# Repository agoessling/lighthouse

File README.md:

lighthouse
==========

48 Output Diasy-Chainable LED Driver.

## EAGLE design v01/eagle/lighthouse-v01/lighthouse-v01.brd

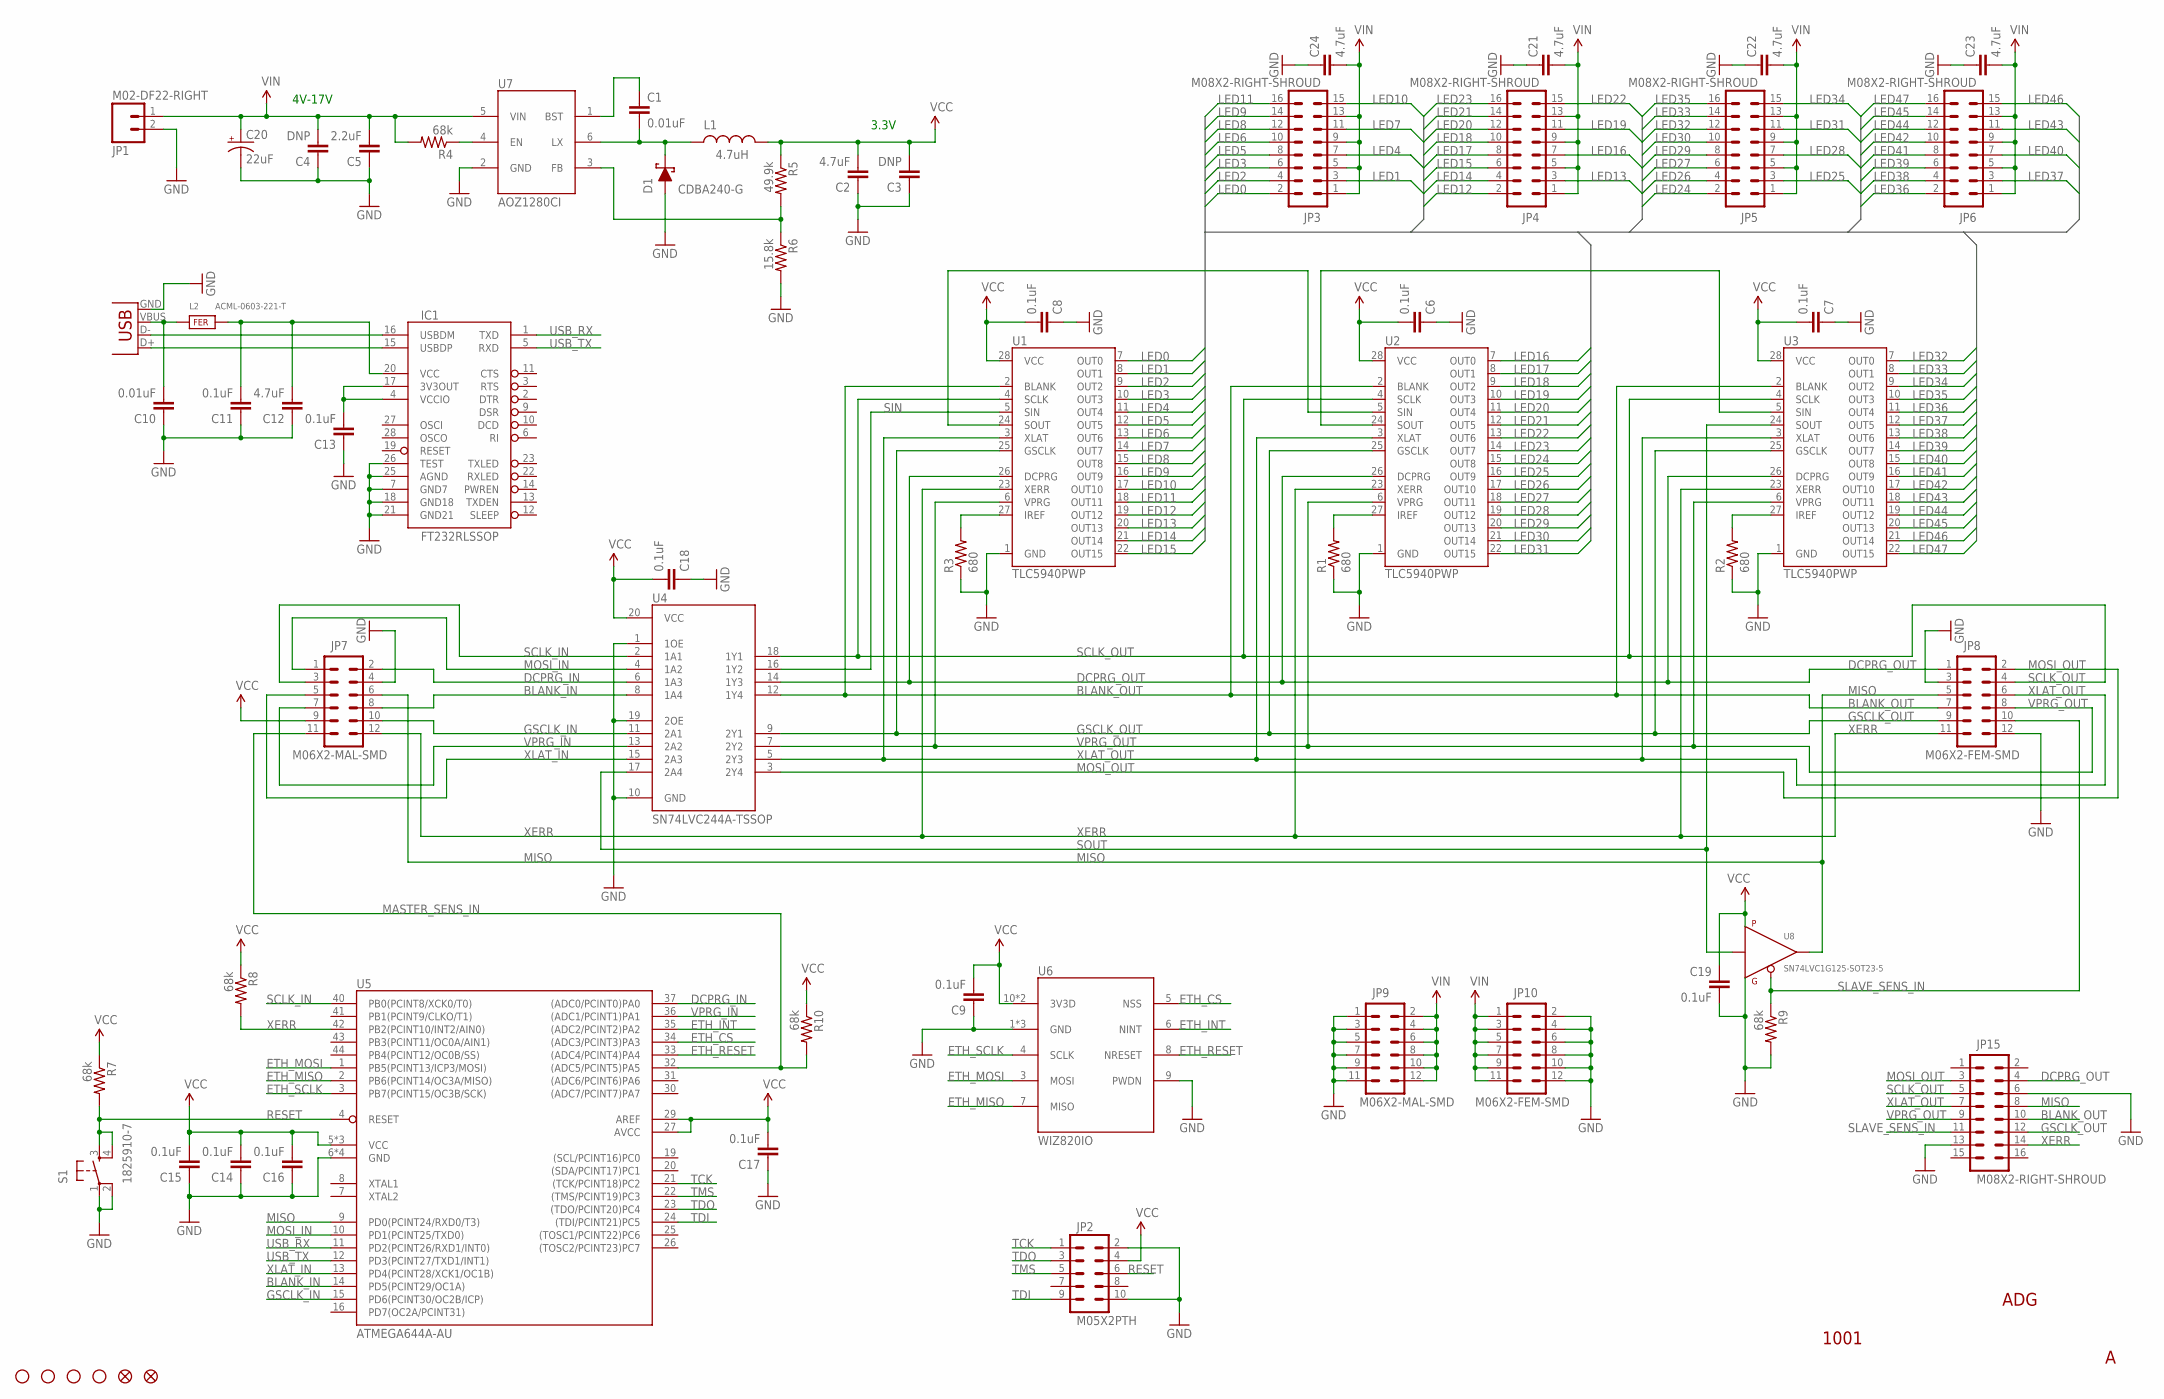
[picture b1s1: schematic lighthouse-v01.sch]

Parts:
C1, C10: 0.01uF; 0603-CAP
C2, C12: 4.7uF; 0805
C3, C4: DNP; 0805
C5: 2.2uF; 0805
C6, C7, C8, C9, C11, C13, C14, C15, C16, C17, C18, C19: 0.1uF; 0603-CAP
C20: 22uF; NIPPON_F80
C21, C22, C23, C24: 4.7uF; 1206
D1: CDBA240-G; DIODE-SMA
IC1: FT232RLSSOP; SSOP28DB
JP1: M02-DF22-RIGHT
JP2: M05X2PTH; AVR_ICSP
JP3, JP4, JP5, JP6, JP15: M08X2-RIGHT-SHROUD; 2X8-RIGHT-SHROUD
JP7, JP9: M06X2-MAL-SMD; 2X6-SMD
JP8, JP10: M06X2-FEM-SMD; 2X6-SMD
JP11, JP12, JP13, JP14: STAND-OFF
JP16, JP17: FIDUCIAL1.5X3; FIDUCIAL-1.5X3
L1: 4.7uH; SRN6045
L2: ACML-0603-221-T; 0603
R1, R2, R3: 680; 0603-RES
R4, R7, R8, R9, R10: 68k; 0603-RES
R5: 49.9k; 0603-RES
R6: 15.8k; 0603-RES
S1: 1825910-7; TACTILE-PTH
U1, U2, U3: TLC5940PWP; TSSOP28-GROUNDPAD
U4: SN74LVC244A-TSSOP; TSSOP-20
U5: ATMEGA644A-AU; TQFP-44
U6: WIZ820IO
U7: AOZ1280CI; SOT23-6
U8: SN74LVC1G125-SOT23-5; SOT23-5
X1: USBSMD; USB-MINIB

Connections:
BLANK_IN: JP7.8, U4.8 (1A4), U5.14 (PD5(PCINT29/OC1A))
BLANK_OUT: JP8.7, JP15.10, U1.2 (BLANK), U2.2 (BLANK), U3.2 (BLANK), U4.12 (1Y4)
DCPRG_IN: JP7.2, U4.6 (1A3), U5.37 ((ADC0/PCINT0)PA0)
DCPRG_OUT: JP8.1, JP15.4, U1.26 (DCPRG), U2.26 (DCPRG), U3.26 (DCPRG), U4.14 (1Y3)
ETH_CS: U5.34 ((ADC3/PCINT3)PA3), U6.5 (NSS)
ETH_INT: U5.35 ((ADC2/PCINT2)PA2), U6.6 (NINT)
ETH_MISO: U5.2 (PB6(PCINT14/OC3A/MISO)), U6.7 (MISO)
ETH_MOSI: U5.1 (PB5(PCINT13/ICP3/MOSI)), U6.3 (MOSI)
ETH_RESET: U5.33 ((ADC4/PCINT4)PA4), U6.8 (NRESET)
ETH_SCLK: U5.3 (PB7(PCINT15/OC3B/SCK)), U6.4 (SCLK)
GND: C2.1, C3.1, C4.1, C5.1, C6.1, C7.1, C8.1, C9.1, C10.1, C11.1, C12.1, C13.1, C14.1, C15.1, C16.1, C17.1, C18.1, C19.2, C20.-, C21.1, C22.1, C23.1, C24.1, D1.A, IC1.7 (GND7), IC1.18 (GND18), IC1.21 (GND21), IC1.25 (AGND), IC1.26 (TEST), JP1.2, JP2.2, JP2.10, JP7.4, JP8.3, JP8.12, JP9.1, JP9.3, JP9.5, JP9.7, JP9.9, JP9.11, JP10.2, JP10.4, JP10.6, JP10.8, JP10.10, JP10.12, JP15.6, JP15.13, R1.1, R2.1, R3.1, R6.2, R9.2, S1.1, S1.2, U1.1 (GND), U2.1 (GND), U3.1 (GND), U4.1 (1OE), U4.10 (GND), U4.19 (2OE), U5.6 (GND), U5.18 (GND), U5.28 (GND), U5.39 (GND), U6.1 (GND), U6.2 (GND), U6.9 (PWDN), U6.12 (GND), U7.2 (GND), U8.3 (GND), X1.GND
GSCLK_IN: JP7.10, U4.11 (2A1), U5.15 (PD6(PCINT30/OC2B/ICP))
GSCLK_OUT: JP8.9, JP15.12, U1.25 (GSCLK), U2.25 (GSCLK), U3.25 (GSCLK), U4.9 (2Y1)
LED0: JP3.2, U1.7 (OUT0)
LED1: JP3.3, U1.8 (OUT1)
LED2: JP3.4, U1.9 (OUT2)
LED3: JP3.6, U1.10 (OUT3)
LED4: JP3.7, U1.11 (OUT4)
LED5: JP3.8, U1.12 (OUT5)
LED6: JP3.10, U1.13 (OUT6)
LED7: JP3.11, U1.14 (OUT7)
LED8: JP3.12, U1.15 (OUT8)
LED9: JP3.14, U1.16 (OUT9)
LED10: JP3.15, U1.17 (OUT10)
LED11: JP3.16, U1.18 (OUT11)
LED12: JP4.2, U1.19 (OUT12)
LED13: JP4.3, U1.20 (OUT13)
LED14: JP4.4, U1.21 (OUT14)
LED15: JP4.6, U1.22 (OUT15)
LED16: JP4.7, U2.7 (OUT0)
LED17: JP4.8, U2.8 (OUT1)
LED18: JP4.10, U2.9 (OUT2)
LED19: JP4.11, U2.10 (OUT3)
LED20: JP4.12, U2.11 (OUT4)
LED21: JP4.14, U2.12 (OUT5)
LED22: JP4.15, U2.13 (OUT6)
LED23: JP4.16, U2.14 (OUT7)
LED24: JP5.2, U2.15 (OUT8)
LED25: JP5.3, U2.16 (OUT9)
LED26: JP5.4, U2.17 (OUT10)
LED27: JP5.6, U2.18 (OUT11)
LED28: JP5.7, U2.19 (OUT12)
LED29: JP5.8, U2.20 (OUT13)
LED30: JP5.10, U2.21 (OUT14)
LED31: JP5.11, U2.22 (OUT15)
LED32: JP5.12, U3.7 (OUT0)
LED33: JP5.14, U3.8 (OUT1)
LED34: JP5.15, U3.9 (OUT2)
LED35: JP5.16, U3.10 (OUT3)
LED36: JP6.2, U3.11 (OUT4)
LED37: JP6.3, U3.12 (OUT5)
LED38: JP6.4, U3.13 (OUT6)
LED39: JP6.6, U3.14 (OUT7)
LED40: JP6.7, U3.15 (OUT8)
LED41: JP6.8, U3.16 (OUT9)
LED42: JP6.10, U3.17 (OUT10)
LED43: JP6.11, U3.18 (OUT11)
LED44: JP6.12, U3.19 (OUT12)
LED45: JP6.14, U3.20 (OUT13)
LED46: JP6.15, U3.21 (OUT14)
LED47: JP6.16, U3.22 (OUT15)
MASTER_SENS_IN: JP7.11, R10.2, U5.32 ((ADC5/PCINT5)PA5)
MISO: JP7.6, JP8.5, JP15.8, U5.9 (PD0(PCINT24/RXD0/T3)), U8.4 (Y)
MOSI_IN: JP7.1, U4.4 (1A2), U5.10 (PD1(PCINT25/TXD0))
MOSI_OUT: JP8.2, JP15.3, U4.3 (2Y4)
unnamed: R3.2, U1.27 (IREF)
unnamed: R1.2, U2.27 (IREF)
unnamed: U2.24 (SOUT), U3.5 (SIN)
unnamed: C1.1, U7.1 (BST)
unnamed: C1.2, D1.C, L1.1, U7.6 (LX)
unnamed: R5.2, R6.1, U7.3 (FB)
unnamed: R4.1, U7.4 (EN)
unnamed: C10.2, L2.1, X1.VBUS
unnamed: C11.2, C12.2, IC1.20 (VCC), L2.2
unnamed: IC1.16 (USBDM), X1.D-
unnamed: IC1.15 (USBDP), X1.D+
unnamed: C13.2, IC1.4 (VCCIO), IC1.17 (3V3OUT)
unnamed: R2.2, U3.27 (IREF)
unnamed: U1.24 (SOUT), U2.5 (SIN)
RESET: JP2.6, R7.2, S1.3, S1.4, U5.4 (RESET)
SCLK_IN: JP7.3, U4.2 (1A1), U5.40 (PB0(PCINT8/XCK0/T0))
SCLK_OUT: JP8.4, JP15.5, U1.4 (SCLK), U2.4 (SCLK), U3.4 (SCLK), U4.18 (1Y1)
SIN: U1.5 (SIN), U4.16 (1Y2)
SLAVE_SENS_IN: JP8.10, JP15.11, R9.1, U8.1 (OE)
SOUT: U3.24 (SOUT), U4.17 (2A4), U8.2 (A)
TCK: JP2.1, U5.21 ((TCK/PCINT18)PC2)
TDI: JP2.9, U5.24 ((TDI/PCINT21)PC5)
TDO: JP2.3, U5.23 ((TDO/PCINT20)PC4)
TMS: JP2.5, U5.22 ((TMS/PCINT19)PC3)
USB_RX: IC1.1 (TXD), U5.11 (PD2(PCINT26/RXD1/INT0))
USB_TX: IC1.5 (RXD), U5.12 (PD3(PCINT27/TXD1/INT1))
VCC: C2.2, C3.2, C6.2, C7.2, C8.2, C9.2, C14.2, C15.2, C16.2, C17.2, C18.2, C19.1, JP2.4, JP7.9, L1.2, R5.1, R7.1, R8.1, R10.1, U1.28 (VCC), U2.28 (VCC), U3.28 (VCC), U4.20 (VCC), U5.5 (VCC), U5.17 (VCC), U5.27 (AVCC), U5.29 (AREF), U5.38 (VCC), U6.10 (3V3D), U6.11 (3V3D), U8.5 (VCC)
VIN: C4.2, C5.2, C20.+, C21.2, C22.2, C23.2, C24.2, JP1.1, JP3.1, JP3.5, JP3.9, JP3.13, JP4.1, JP4.5, JP4.9, JP4.13, JP5.1, JP5.5, JP5.9, JP5.13, JP6.1, JP6.5, JP6.9, JP6.13, JP9.2, JP9.4, JP9.6, JP9.8, JP9.10, JP9.12, JP10.1, JP10.3, JP10.5, JP10.7, JP10.9, JP10.11, R4.2, U7.5 (VIN)
VPRG_IN: JP7.7, U4.13 (2A2), U5.36 ((ADC1/PCINT1)PA1)
VPRG_OUT: JP8.8, JP15.9, U1.6 (VPRG), U2.6 (VPRG), U3.6 (VPRG), U4.7 (2Y2)
XERR: JP7.12, JP8.11, JP15.14, R8.2, U1.23 (XERR), U2.23 (XERR), U3.23 (XERR), U5.42 (PB2(PCINT10/INT2/AIN0))
XLAT_IN: JP7.5, U4.15 (2A3), U5.13 (PD4(PCINT28/XCK1/OC1B))
XLAT_OUT: JP8.6, JP15.7, U1.3 (XLAT), U2.3 (XLAT), U3.3 (XLAT), U4.5 (2Y3)

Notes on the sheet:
3.3V
4V-17V
ADG
1001

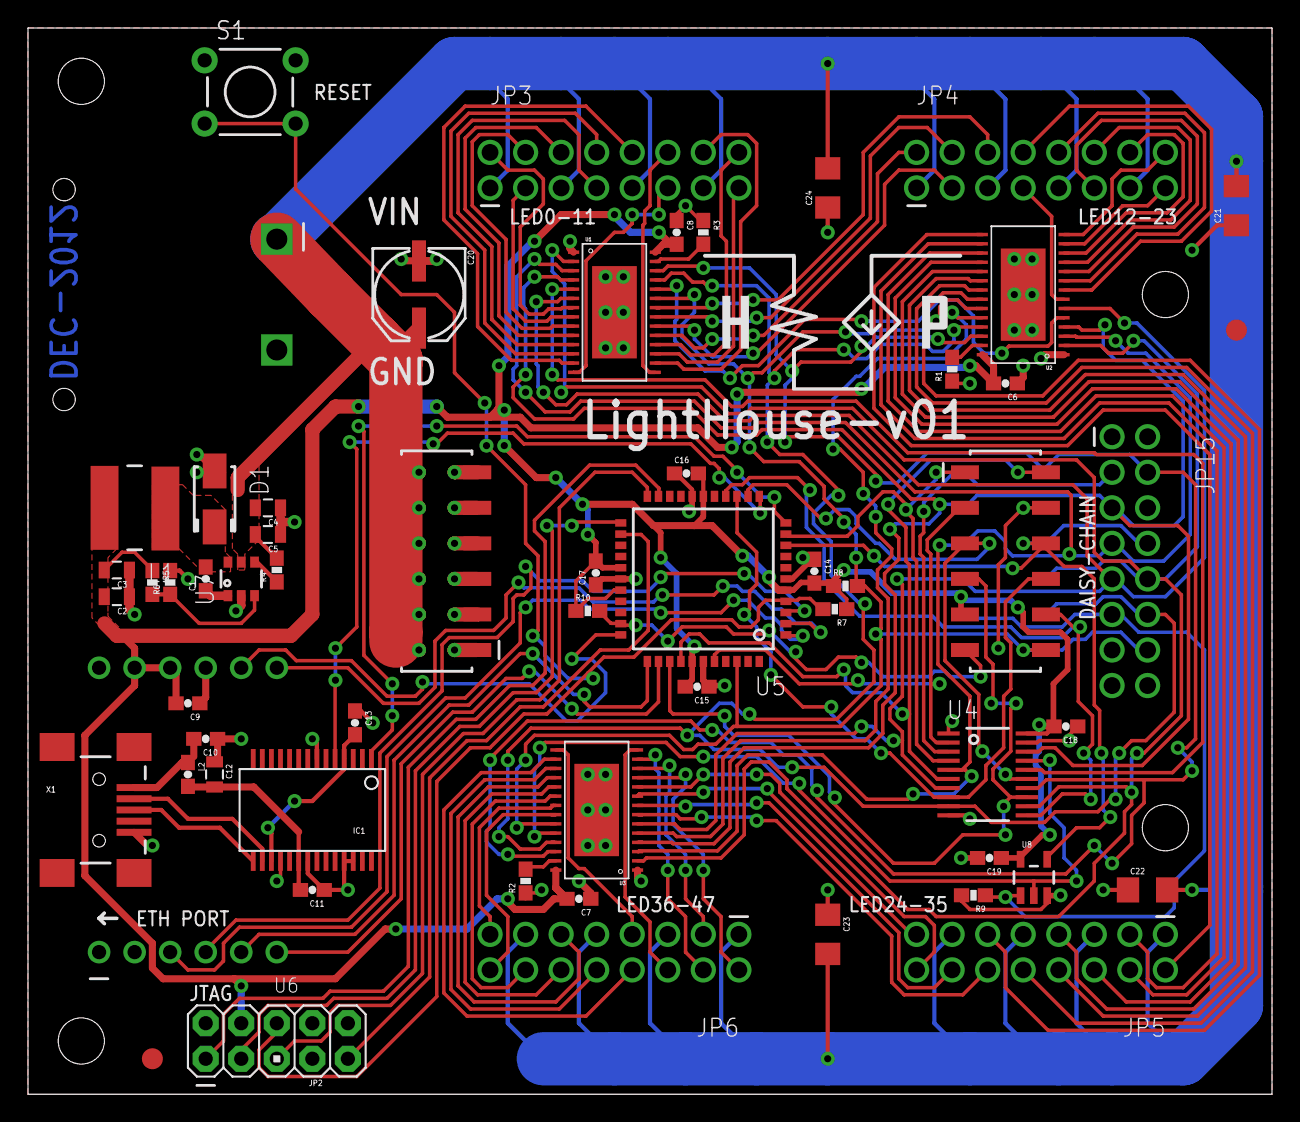
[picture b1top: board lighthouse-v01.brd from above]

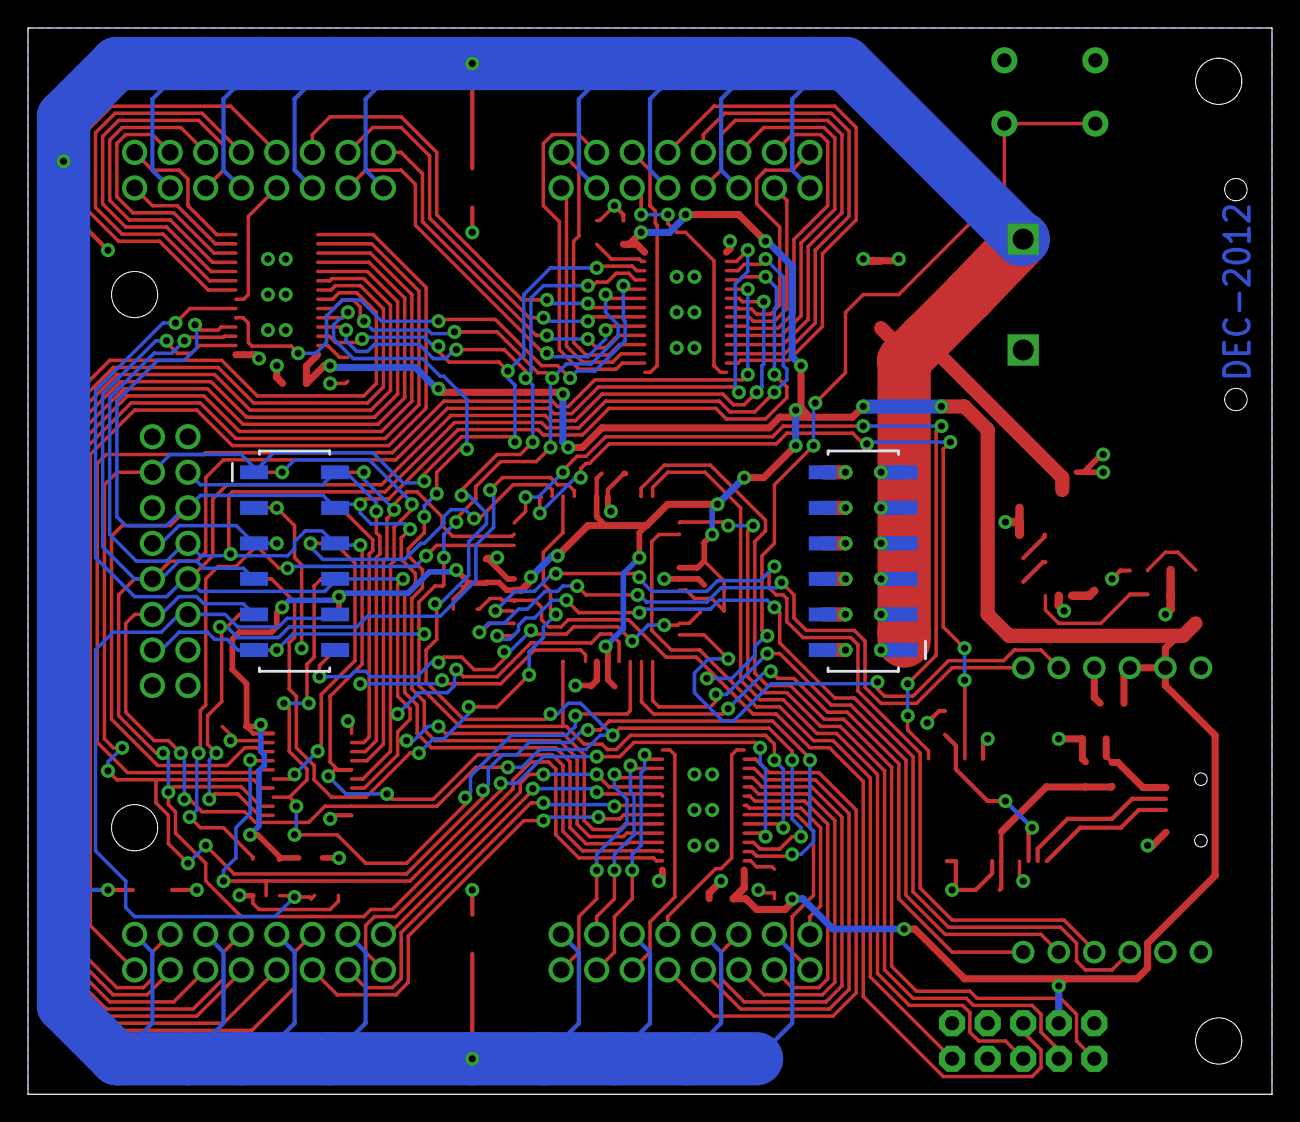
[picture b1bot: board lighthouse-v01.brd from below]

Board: 2 copper layers, 88.9 x 76.2 mm, 66 parts (2 on the bottom side), 98 nets.

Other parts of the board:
U$9: HYBRIDPI_LOGO_MED

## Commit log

2012-12-22 Initial Push
2012-12-22 Made Order
2012-12-22 Changed TSSOP-28 Reference
2012-12-22 Made Digi-Key Order

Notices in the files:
parts and their libraries:
SparkFun: Licensing: CC v3.0 Share-Alike You are welcome to use this library for commercial purposes.
